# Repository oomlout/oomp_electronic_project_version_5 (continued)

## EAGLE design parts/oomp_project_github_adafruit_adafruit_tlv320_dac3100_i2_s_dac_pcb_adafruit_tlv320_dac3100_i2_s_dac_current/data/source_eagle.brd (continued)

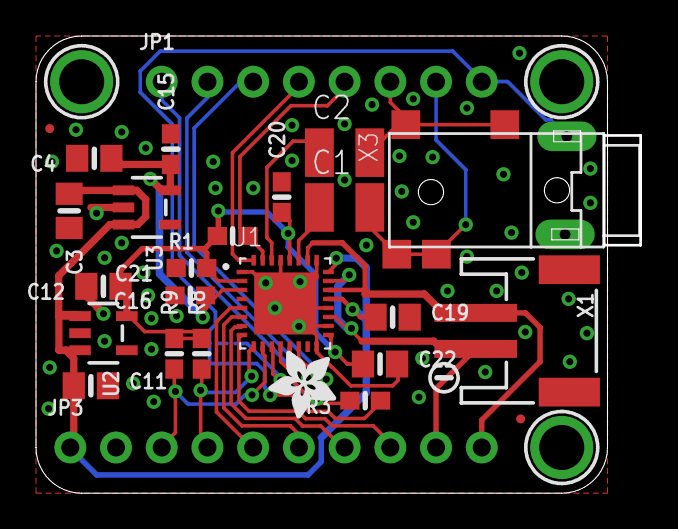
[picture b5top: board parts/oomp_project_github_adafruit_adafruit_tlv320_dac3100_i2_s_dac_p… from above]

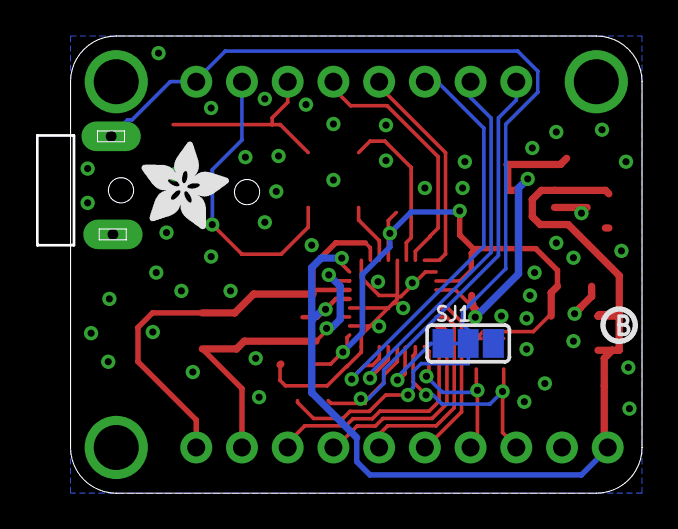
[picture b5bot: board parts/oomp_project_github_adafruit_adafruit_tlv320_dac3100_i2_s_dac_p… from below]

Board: 2 copper layers, 33.6 x 25.4 mm, 60 parts (10 on the bottom side), 23 nets.

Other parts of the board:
E$1: SYMBOL_MINUS
PLABEL0: PLABEL0
PLABEL1: PLABEL1
PLABEL2: PLABEL2
PLABEL3: PLABEL3
PLABEL4: PLABEL4
PLABEL5: PLABEL5
PLABEL6: PLABEL6
PLABEL7: PLABEL7
PLABEL8: PLABEL8
PLABEL9: PLABEL9
PLABEL10: PLABEL10
PLABEL11: PLABEL11
PLABEL12: PLABEL12
PLABEL13: PLABEL13
PLABEL14: PLABEL14
PLABEL15: PLABEL15
PLABEL16: PLABEL16
PLABEL17: PLABEL17
PLABEL18: PLABEL18
PLABEL19: PLABEL19
PLABEL20: PLABEL20
PLABEL21: PLABEL21
PLABEL22: PLABEL22
PLABEL23: PLABEL23
PLABEL24: PLABEL24
PLABEL25: PLABEL25
PLABEL26: PLABEL26
U$5: PCBFEAT-REV-040
U$6: ADAFRUIT_5MM
U$29: ADAFRUIT_3.5MM

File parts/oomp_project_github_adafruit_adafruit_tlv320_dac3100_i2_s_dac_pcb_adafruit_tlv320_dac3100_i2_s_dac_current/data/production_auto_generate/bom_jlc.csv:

Comment,Designator,Footprint,LCSC Part #
,JP1,Adafruit TLV320DAC3100 I2S DAC-import-fps:1X08_ROUND_70,C492421
,JP3,Adafruit TLV320DAC3100 I2S DAC-import-fps:1X10_ROUND70,C57369
,U$29,Adafruit TLV320DAC3100 I2S DAC-import-fps:ADAFRUIT_3.5MM,
,U$6,Adafruit TLV320DAC3100 I2S DAC-import-fps:ADAFRUIT_5MM,
,U$5,Adafruit TLV320DAC3100 I2S DAC-import-fps:PCBFEAT-REV-040,
,PLABEL0,Adafruit TLV320DAC3100 I2S DAC-import-fps:PLABEL0,
,PLABEL1,Adafruit TLV320DAC3100 I2S DAC-import-fps:PLABEL1,
,PLABEL10,Adafruit TLV320DAC3100 I2S DAC-import-fps:PLABEL10,
,PLABEL11,Adafruit TLV320DAC3100 I2S DAC-import-fps:PLABEL11,
,PLABEL12,Adafruit TLV320DAC3100 I2S DAC-import-fps:PLABEL12,
,PLABEL13,Adafruit TLV320DAC3100 I2S DAC-import-fps:PLABEL13,
,PLABEL14,Adafruit TLV320DAC3100 I2S DAC-import-fps:PLABEL14,
,PLABEL15,Adafruit TLV320DAC3100 I2S DAC-import-fps:PLABEL15,
,PLABEL16,Adafruit TLV320DAC3100 I2S DAC-import-fps:PLABEL16,
,PLABEL17,Adafruit TLV320DAC3100 I2S DAC-import-fps:PLABEL17,
,PLABEL18,Adafruit TLV320DAC3100 I2S DAC-import-fps:PLABEL18,
,PLABEL19,Adafruit TLV320DAC3100 I2S DAC-import-fps:PLABEL19,
,PLABEL2,Adafruit TLV320DAC3100 I2S DAC-import-fps:PLABEL2,
,PLABEL20,Adafruit TLV320DAC3100 I2S DAC-import-fps:PLABEL20,
,PLABEL21,Adafruit TLV320DAC3100 I2S DAC-import-fps:PLABEL21,
,PLABEL22,Adafruit TLV320DAC3100 I2S DAC-import-fps:PLABEL22,
,PLABEL23,Adafruit TLV320DAC3100 I2S DAC-import-fps:PLABEL23,
,PLABEL24,Adafruit TLV320DAC3100 I2S DAC-import-fps:PLABEL24,
,PLABEL25,Adafruit TLV320DAC3100 I2S DAC-import-fps:PLABEL25,
,PLABEL26,Adafruit TLV320DAC3100 I2S DAC-import-fps:PLABEL26,
,PLABEL3,Adafruit TLV320DAC3100 I2S DAC-import-fps:PLABEL3,
,PLABEL4,Adafruit TLV320DAC3100 I2S DAC-import-fps:PLABEL4,
,PLABEL5,Adafruit TLV320DAC3100 I2S DAC-import-fps:PLABEL5,
,PLABEL6,Adafruit TLV320DAC3100 I2S DAC-import-fps:PLABEL6,
,PLABEL7,Adafruit TLV320DAC3100 I2S DAC-import-fps:PLABEL7,
,PLABEL8,Adafruit TLV320DAC3100 I2S DAC-import-fps:PLABEL8,
,PLABEL9,Adafruit TLV320DAC3100 I2S DAC-import-fps:PLABEL9,
,E$1,Adafruit TLV320DAC3100 I2S DAC-import-fps:SYMBOL_MINUS,
0.1uF,"C15,C16,C20,C21",Adafruit TLV320DAC3100 I2S DAC-import-fps:0603-NO,C14663
100uF/6.3V,"C1,C2",Adafruit TLV320DAC3100 I2S DAC-import-fps:C1210,
10k,"R1,R8,R9",Adafruit TLV320DAC3100 I2S DAC-import-fps:0603-NO,C98220
10uF,"C3,C4,C11,C12,C19,C22",Adafruit TLV320DAC3100 I2S DAC-import-fps:0805-NO,
2.2K,R3,Adafruit TLV320DAC3100 I2S DAC-import-fps:0603-NO,C4190
AP2127K-1.8,U3,Adafruit TLV320DAC3100 I2S DAC-import-fps:SOT23-5,
AP2127K-3.3,U2,Adafruit TLV320DAC3100 I2S DAC-import-fps:SOT23-5,
CON_JST_PH_2PIN_MTPH2,X1,Adafruit TLV320DAC3100 I2S DAC-import-fps:JSTPH2,
TLV320DAC3100,U1,Adafruit TLV320DAC3100 I2S DAC-import-fps:TLV320DAC3100,
TRRS_2SWITCH_PJ332A,X3,Adafruit TLV320DAC3100 I2S DAC-import-fps:PJ-332A,

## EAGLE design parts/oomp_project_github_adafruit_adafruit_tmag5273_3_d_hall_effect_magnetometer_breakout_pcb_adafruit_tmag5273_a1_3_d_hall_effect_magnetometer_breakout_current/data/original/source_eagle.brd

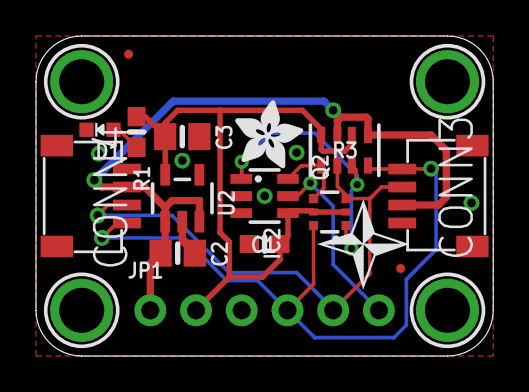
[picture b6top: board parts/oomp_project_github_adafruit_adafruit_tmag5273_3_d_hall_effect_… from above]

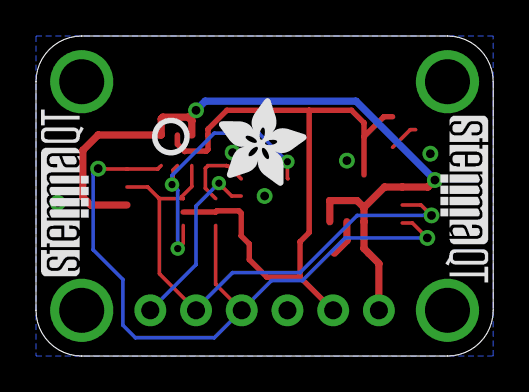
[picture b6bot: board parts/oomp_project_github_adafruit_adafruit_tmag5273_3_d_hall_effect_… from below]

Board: 2 copper layers, 25.4 x 17.8 mm, 39 parts (8 on the bottom side), 9 nets.

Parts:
C1: 0.1uF; 0603-NO
C2, C3: 10uF; 0805-NO
CONN3, CONN4: STEMMA_I2C_QT; JST_SH4
D1: GREEN; CHIPLED_0603_NOOUTLINE
FID3, FID4: FIDUCIAL_0.5MM
IC2: TMAG5273A1; SOT23-6
JP1: 1X06_ROUND_70
PLABEL0: PLABEL0
PLABEL1: PLABEL1
PLABEL2: PLABEL2
PLABEL3: PLABEL3
PLABEL4: PLABEL4
PLABEL6: PLABEL6
PLABEL7: PLABEL7
PLABEL8: PLABEL8
PLABEL9: PLABEL9
PLABEL10: PLABEL10
PLABEL11: PLABEL11
PLABEL12: PLABEL12
PLABEL13: PLABEL13
PLABEL14: PLABEL14
PLABEL15: PLABEL15
Q2: BSS138; SOT363
R1: 10K; 0603-NO
R3: 10K pack; RESPACK_4X0603
U2: AP2127K-3.3; SOT23-5
U$1, U$17, U$19, U$21: MOUNTINGHOLE2.5; MOUNTINGHOLE_2.5_PLATED
U$2: SYMBOL_COMPASSXY_5MM
U$4: ADAFRUIT_5MM
U$22: ADAFRUIT_3.5MM
U$25: PCBFEAT-REV-040
U$30, U$31: STEMMAQT

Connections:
3.3V: C1.1, C3.1, IC2.4, JP1.2, Q2.2, Q2.5, R1.1, R3.2, R3.4, U2.5
!INT: IC2.5, JP1.6
GND: C1.2, C2.2, C3.2, CONN3.1, CONN3.MT1, CONN3.MT2, CONN4.1, CONN4.MT1, CONN4.MT2, D1.C, IC2.2, IC2.3, JP1.3, U2.2
unnamed: D1.A, R1.2
SCL: CONN3.4, CONN4.4, JP1.4, Q2.6, R3.8
SCL_3V: IC2.1, Q2.1, R3.7
SDA: CONN3.3, CONN4.3, JP1.5, Q2.3, R3.6
SDA_3V: IC2.6, Q2.4, R3.5
VCC: C2.1, CONN3.2, CONN4.2, JP1.1, R3.1, R3.3, U2.1, U2.3

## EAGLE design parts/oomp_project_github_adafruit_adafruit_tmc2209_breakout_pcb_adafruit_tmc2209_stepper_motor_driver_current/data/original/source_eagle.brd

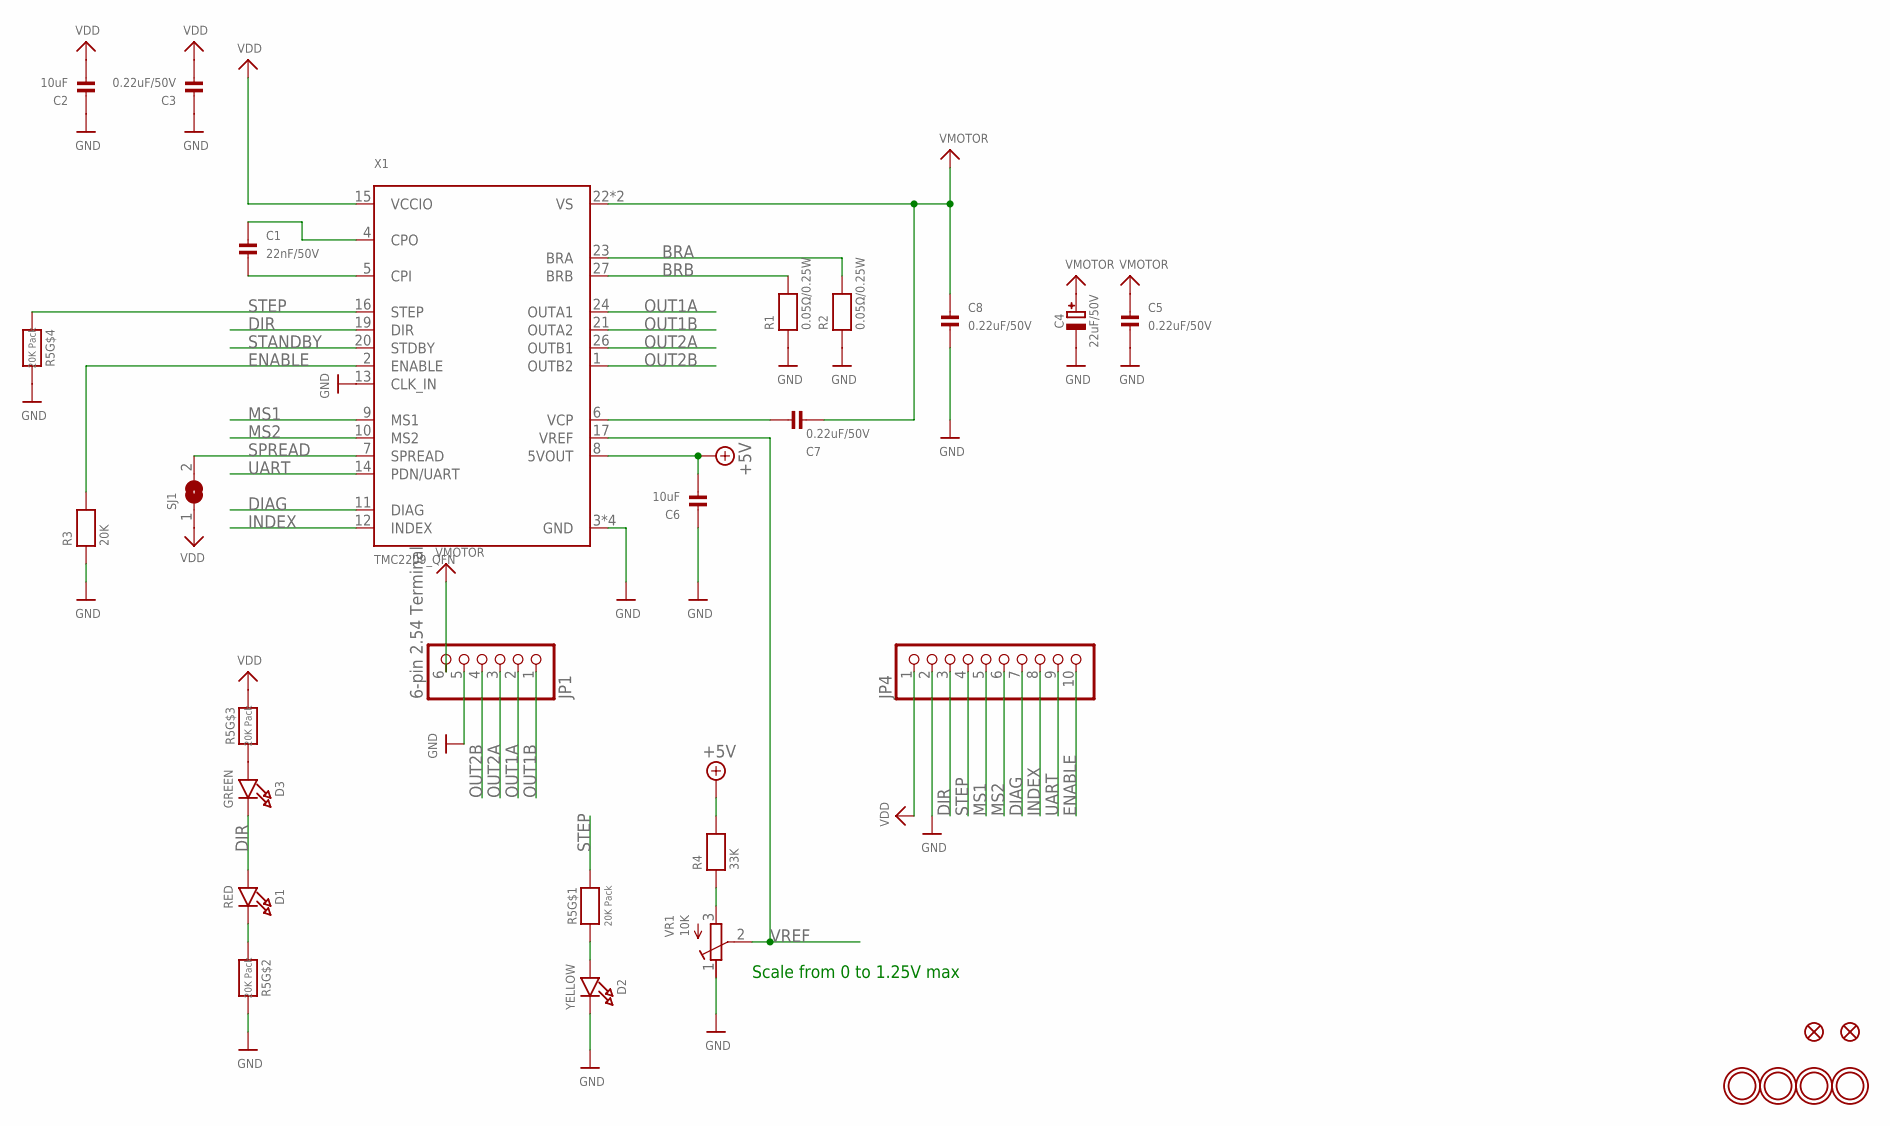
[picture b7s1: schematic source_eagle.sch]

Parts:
C1: 22nF/50V; 0603-NO
C2, C6: 10uF; 0805-NO
C3, C5, C7, C8: 0.22uF/50V; 0603-NO
C4: 22uF/50V; PANASONIC_C
D1: RED; CHIPLED_0603_NOOUTLINE
D2: YELLOW; CHIPLED_0603_NOOUTLINE
D3: GREEN; CHIPLED_0603_NOOUTLINE
JP1: 6-pin 2.54 Terminal; 1X06_2.54MMTERMINAL
JP4: HEADER-1X1070MIL; 1X10_ROUND70
R1, R2: 0.05Ω/0.25W; 0603-NO
R3: 20K; 0603-NO
R4: 33K; 0603-NO
R5: 20K Pack; RESPACK_4X0603
SJ1: SOLDERJUMPER; SOLDERJUMPER_ARROW_NOPASTE
U$10, U$11: FIDUCIAL_0.5MM
U$18, U$22, U$26, U$27: MOUNTINGHOLE2.0; MOUNTINGHOLE_2.0_PLATED
VR1: 10K; RTRIM3314J
X1: TMC2209_QFN; QFN28_5MM_MICROCHIP

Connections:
+5V: C6.2, R4.2, X1.8 (5VOUT)
BRA: R2.2, X1.23 (BRA)
BRB: R1.2, X1.27 (BRB)
DIAG: JP4.7, X1.11 (DIAG)
DIR: D1.A, D3.C, JP4.3, X1.19 (DIR)
ENABLE: JP4.10, R3.2, X1.2 (ENABLE)
GND: C2.1, C3.1, C4.-, C5.2, C6.1, C8.2, D2.C, JP1.5, JP4.2, R1.1, R2.1, R3.1, R5.5 (2), R5.7 (2), VR1.1 (E), X1.3 (GND), X1.13 (CLK_IN), X1.18 (GND), X1.25 (GND), X1.THERMAL (GND)
INDEX: JP4.8, X1.12 (INDEX)
MS1: JP4.5, X1.9 (MS1)
MS2: JP4.6, X1.10 (MS2)
unnamed: D2.A, R5.1
unnamed: C1.1, X1.4 (CPO)
unnamed: C1.2, X1.5 (CPI)
unnamed: R4.1, VR1.3 (A)
unnamed: C7.1, X1.6 (VCP)
unnamed: D1.C, R5.2 (1)
unnamed: D3.A, R5.3 (1)
OUT1A: JP1.2, X1.24 (OUTA1)
OUT1B: JP1.1, X1.21 (OUTA2)
OUT2A: JP1.3, X1.26 (OUTB1)
OUT2B: JP1.4, X1.1 (OUTB2)
SPREAD: SJ1.2, X1.7 (SPREAD)
STANDBY: X1.20 (STDBY)
STEP: JP4.4, R5.4 (1), R5.8 (2), X1.16 (STEP)
UART: JP4.9, X1.14 (PDN/UART)
VDD: C2.2, C3.2, JP4.1, R5.6 (2), SJ1.1, X1.15 (VCCIO)
VMOTOR: C4.+, C5.1, C7.2, C8.1, JP1.6, X1.22 (VS), X1.28 (VS)
VREF: VR1.2 (S), X1.17 (VREF)

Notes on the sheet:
Scale from 0 to 1.25V max

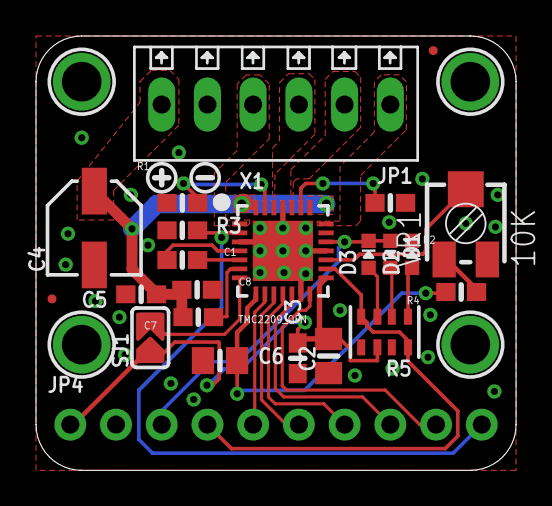
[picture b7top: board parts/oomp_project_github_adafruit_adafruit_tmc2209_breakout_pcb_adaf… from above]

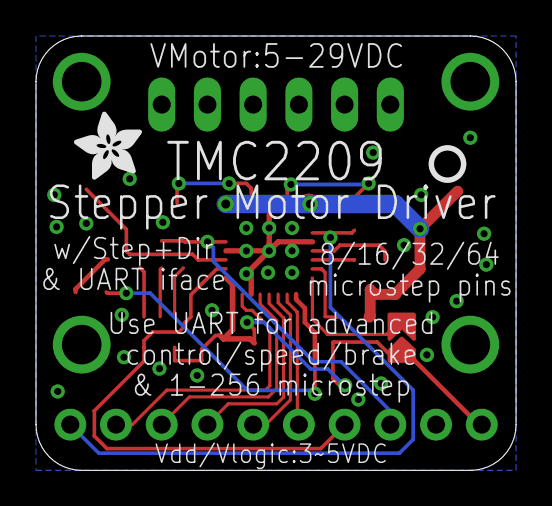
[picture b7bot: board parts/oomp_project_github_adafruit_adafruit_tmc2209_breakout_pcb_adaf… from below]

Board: 2 copper layers, 26.7 x 24.1 mm, 52 parts (2 on the bottom side), 27 nets.

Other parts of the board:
PLABEL0: PLABEL0
PLABEL1: PLABEL1
PLABEL2: PLABEL2
PLABEL3: PLABEL3
PLABEL4: PLABEL4
PLABEL5: PLABEL5
PLABEL6: PLABEL6
PLABEL7: PLABEL7
PLABEL8: PLABEL8
PLABEL9: PLABEL9
PLABEL10: PLABEL10
PLABEL11: PLABEL11
PLABEL12: PLABEL12
PLABEL13: PLABEL13
PLABEL14: PLABEL14
PLABEL15: PLABEL15
PLABEL16: PLABEL16
PLABEL17: PLABEL17
PLABEL18: PLABEL18
PLABEL19: PLABEL19
PLABEL20: PLABEL20
U$7: SYMBOL_PLUS
U$8: SYMBOL_MINUS
U$12: PCBFEAT-REV-040
U$24: ADAFRUIT_3.5MM
